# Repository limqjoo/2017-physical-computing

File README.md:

# Physical Computing - Lab Assignments and Final Project (2017)

This repository archives the lab assignments and final project completed during the IS53030A Physical Computing module at Goldsmiths University in 2017. The projects in this repository showcase the skills and knowledge acquired throughout the course.

## Table of Contents

- [Lab Assignments](#lab-assignments)
- [Final Project](#final-project)
- [Getting Started](#getting-started)
- [License](#license)

## Lab Assignments

The lab assignments in this repository demonstrate practical applications of physical computing concepts. Each assignment is organized into separate directories.

1. **Lab 1: Introduction to Arduino**
   - Overview of basic Arduino programming and hardware interaction.

2. **Lab 2: Analog Input & Output**
   - Exploration of analog sensors and actuators.

3. **Lab 3: Digital Input & Output**
   - Understanding digital sensors and output devices.

4. **Lab 4: Serial Communication**
   - Implementation of serial communication between Arduino and other devices.

5. **Lab 5: Interactivity & Interface**
   - Integration of sensors for interactive applications.

6. **Lab 6: Motors & Transistors**
   - Control of motors using transistors and other electronic components.

7. **Lab 7: Final Lab Assignment**
   - Culmination of skills learned in previous labs to create a comprehensive project.

## Final Project

The final project directory contains the culmination of the skills acquired during the Physical Computing module. The project description, source code, and any additional documentation are available to provide insights into the creative and technical aspects of the final work.

**Note: This repository is intended for documentation purposes only and is not meant to be cloned. To access specific project details, navigate to the relevant directories within the documentation.**

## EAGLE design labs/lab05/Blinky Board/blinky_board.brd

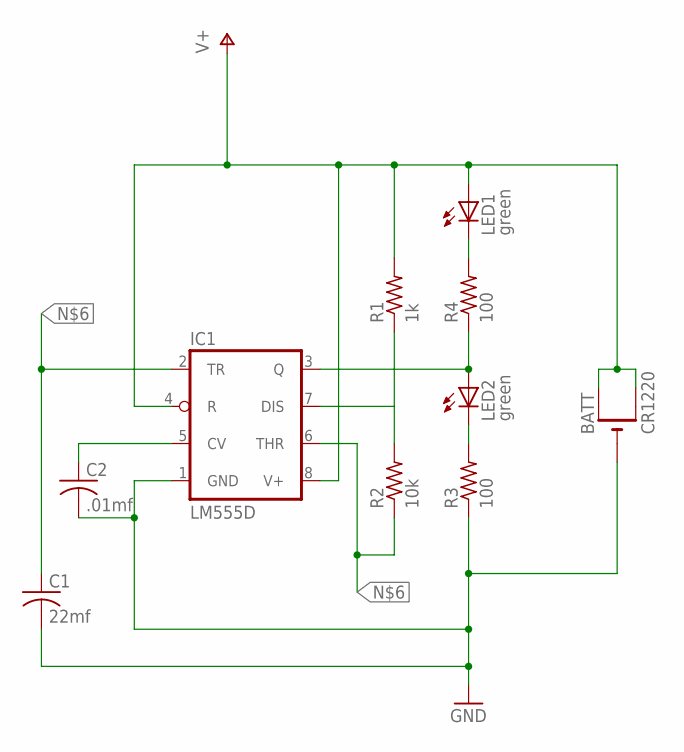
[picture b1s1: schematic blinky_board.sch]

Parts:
BATT: CR1220; CR1220-SMD; MPN 3000
C1: 22mf; C0805K; MPN HBA22MFZRE
C2: .01mf; C0805K; MPN 60R185XF
IC1: LM555D; SO08; MPN LM555CMX/NOPB.
LED1, LED2: green; CHIPLED_0805; MPN KPHCM-2012CGCK
R1: 1k; R0805; MPN CRCW06031K00FKEA
R2: 10k; R0805; MPN MFR4-10KFI
R3, R4: 100; R0805; MPN RC0402JR-13100RL

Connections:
GND: BATT.-, C1.2, C2.2, IC1.1 (GND), R3.1
unnamed: C2.1, IC1.5 (CV)
unnamed: IC1.3 (Q), LED2.A, R4.1
unnamed: LED2.C, R3.2
unnamed: LED1.C, R4.2
unnamed: IC1.7 (DIS), R1.1, R2.2
unnamed: C1.1, IC1.2 (TR), IC1.6 (THR), R2.1
V+: BATT.+$1 (+), BATT.+$2 (+1), IC1.4 (R), IC1.8 (V+), LED1.A, R1.2

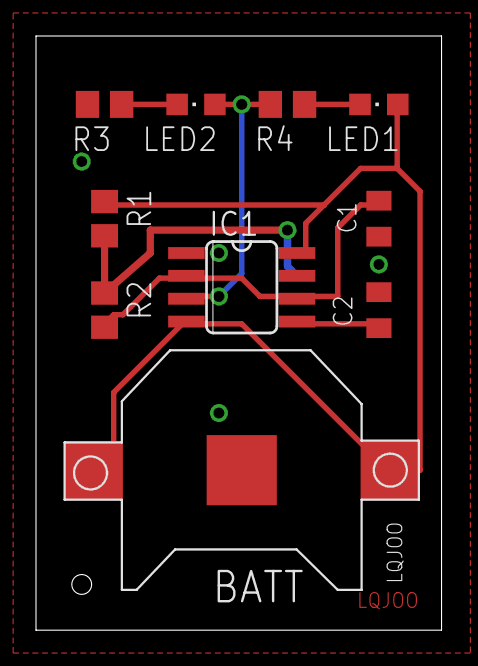
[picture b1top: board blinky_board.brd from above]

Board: 2 copper layers, 22.5 x 33.0 mm, 10 parts (0 on the bottom side), 8 nets.

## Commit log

2020-07-29 added all archived assignments and projects
2024-01-07 reorganized files and removed MPR121
